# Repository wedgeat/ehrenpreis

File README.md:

# Ehrenpreis — electronic chime module

**A compact, programmable audio module for embedded projects, built around the NXP LPC802 microcontroller.**

Ehrenpreis explores a practical middle ground between a simple piezo buzzer and a full digital audio subsystem. It provides embedded projects with distinctive, programmable sound effects without a single board computer, an I²S audio interface or a dedicated high-performance audio processor.

The design uses a low-cost microcontroller to generate audio through PWM. A passive second-order RC low-pass filter reconstructs the signal, which is then AC-coupled and amplified by a dedicated audio amplifier. The firmware is written in C, with a lookup-table-based waveform generator and configurable sound envelopes.

The hardware and firmware are developed as an open project.

The repository is organised into two parts:

- hardware/ – Hardware design files for the electronic chime module.
- firmware/ – Embedded firmware for the LPC802 microcontroller.

A blog post on wedge.at documents the development process and the decisions behind the project.

License: BSD 3-Clause. See LICENSE for details.

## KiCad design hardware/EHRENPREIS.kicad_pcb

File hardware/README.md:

HARDWARE
Ehrenpreis Electronic Chime Module

This folder contains the hardware design files for the Ehrenpreis electronic chime module, built around the NXP LPC802 microcontroller.

The hardware is developed specifically for this project and forms the physical foundation of the electronic chime.

For an overview of the project and the development process, see the blog post on wedge.at.

See the repository root for general project information and licensing.

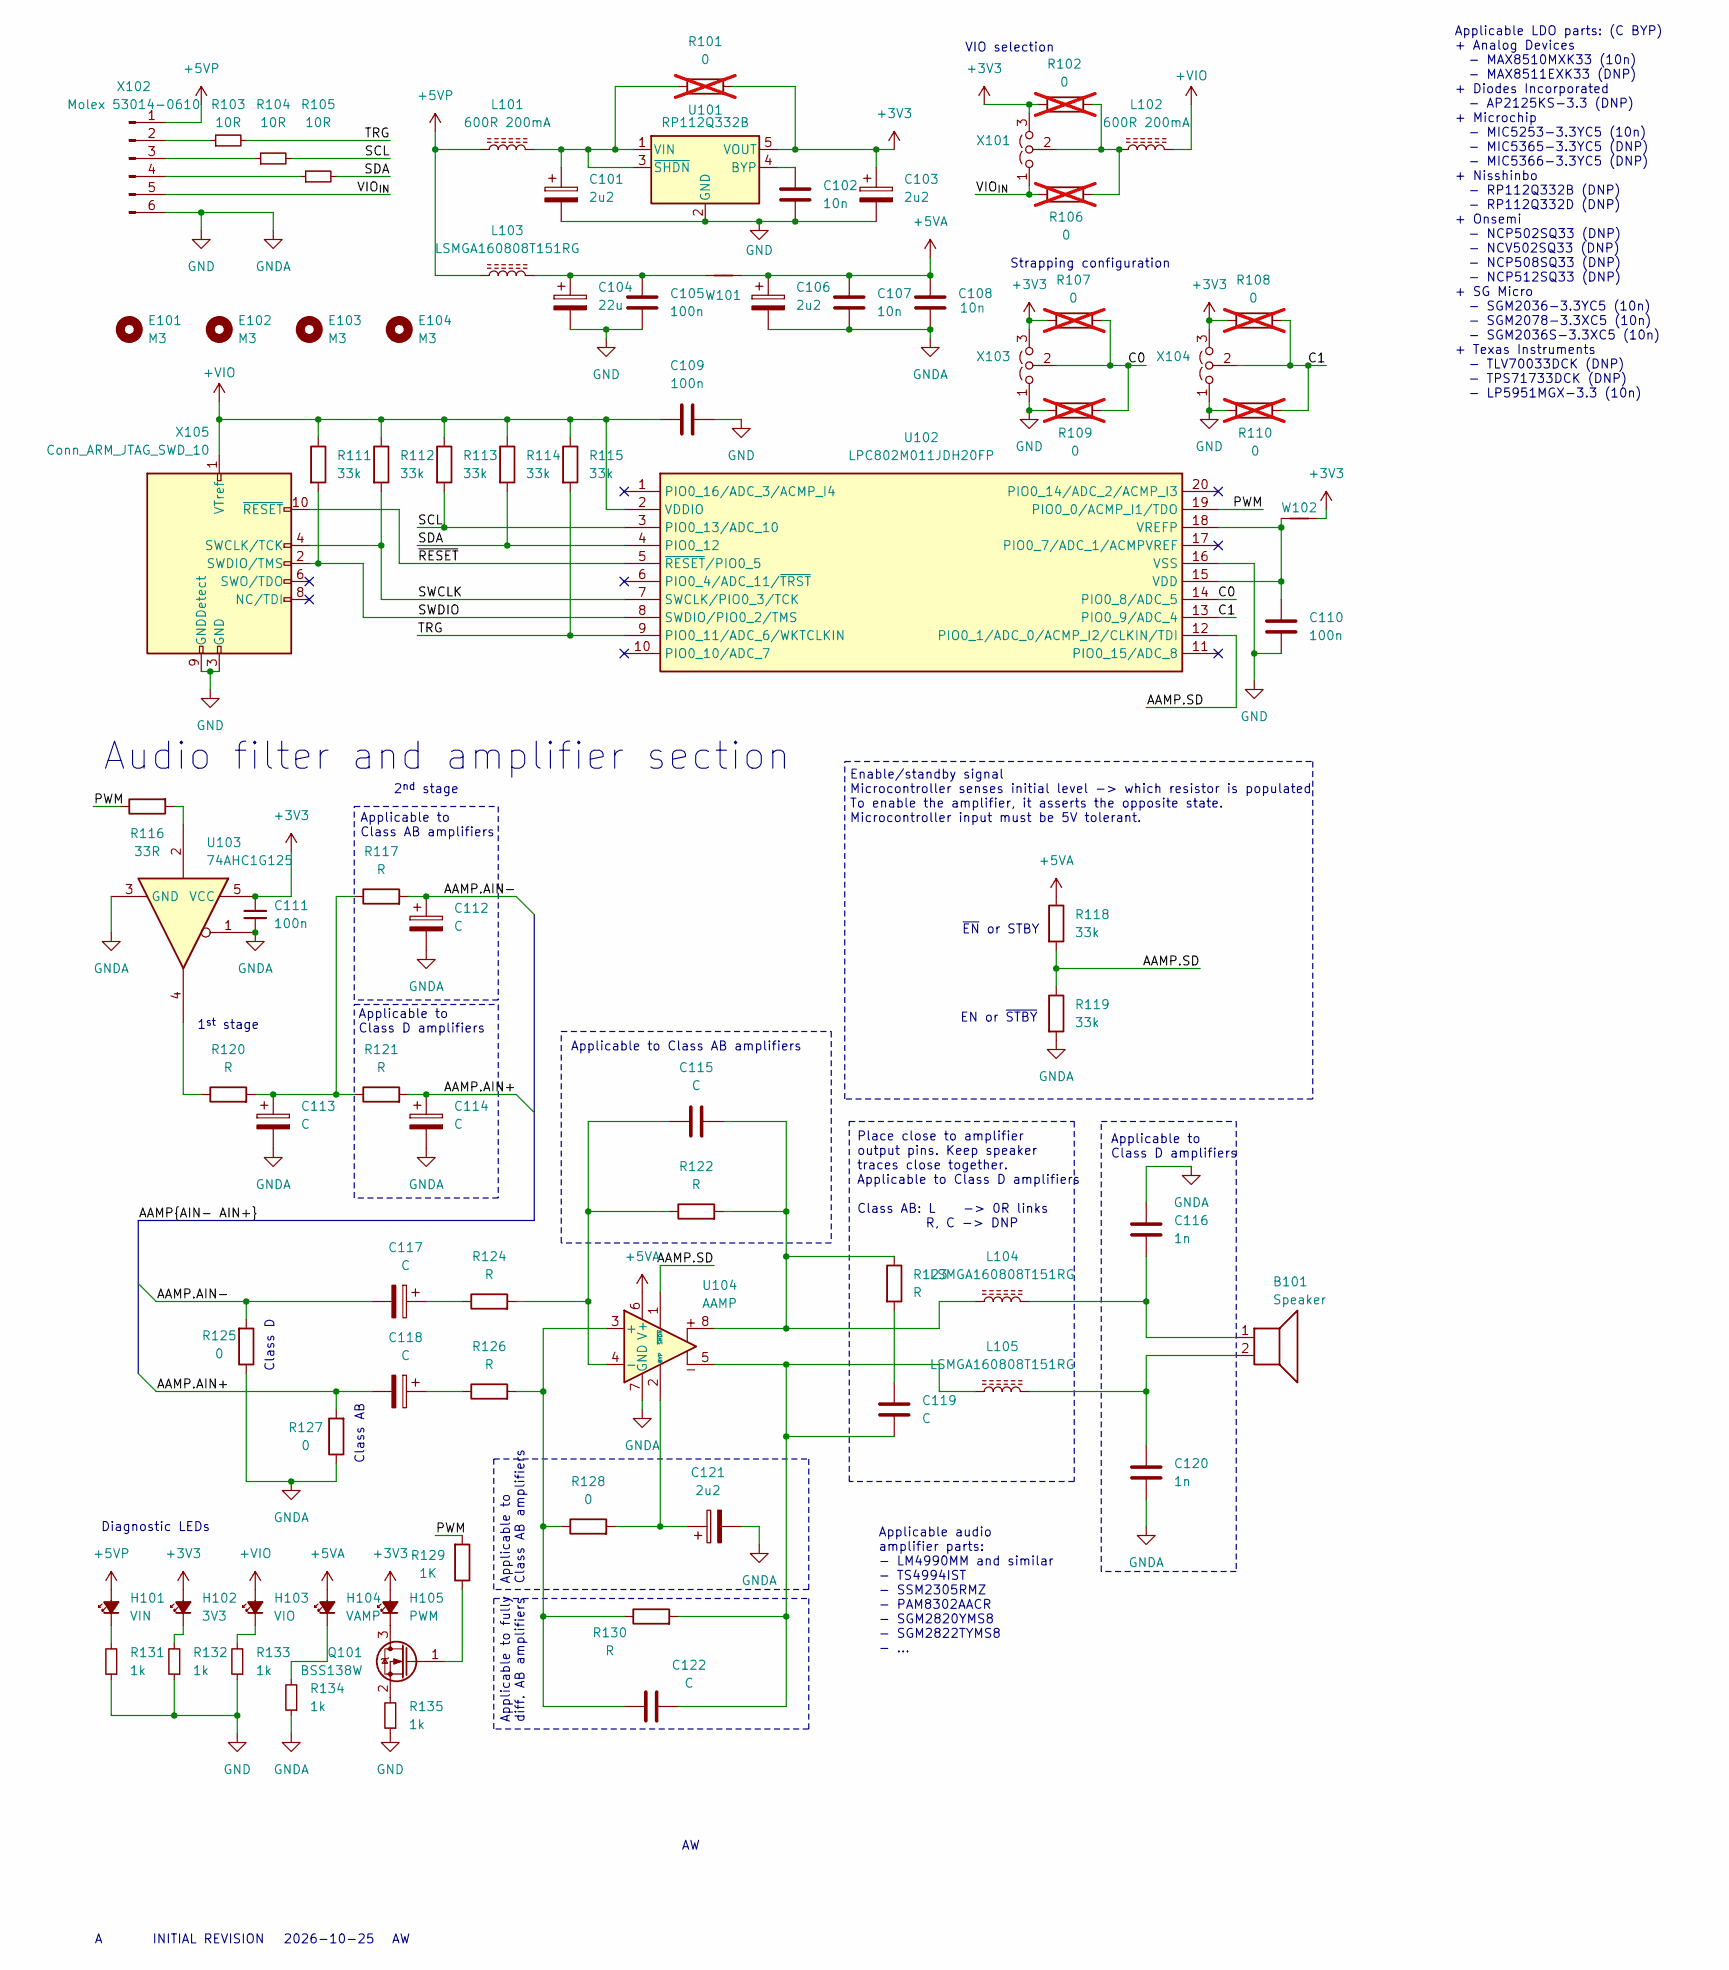
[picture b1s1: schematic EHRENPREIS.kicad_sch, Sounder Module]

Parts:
B101: Speaker; JST_XH_B2B-XH-A_1x02_P2.50mm_Vertical
C101, C103, C106, C121: 2u2; CP_EIA-3216-18_Kemet-A
C102, C107, C108: 10n; C_0603_1608Metric
C104: 22u; CP_EIA-7343-31_Kemet-D
C105, C109, C110, C111: 100n; C_0603_1608Metric
C112, C113, C114, C117, C118: C; CP_EIA-3216-18_Kemet-A
C115, C119, C122: C; C_0603_1608Metric
C116, C120: 1n; C_0603_1608Metric
E101, E102, E103, E104: M3; MountingHole_3.2mm_M3_DIN965
H101: VIN; LED_0603_1608Metric
H102: 3V3; LED_0603_1608Metric
H103: VIO; LED_0603_1608Metric
H104: VAMP; LED_0603_1608Metric
H105: PWM; LED_0603_1608Metric
L101, L102: 600R 200mA; L_0603_1608Metric
L103, L104, L105: LSMGA160808T151RG; L_0603_1608Metric
Q101: BSS138W; SOT-323_SC-70
R101, R102, R106, R107, R108, R109, R110: 0; R_0603_1608Metric; not fitted
R103, R104, R105: 10R; R_0603_1608Metric
R111, R112, R113, R114, R115, R118, R119: 33k; R_0603_1608Metric
R116: 33R; R_0603_1608Metric
R117, R120, R121, R122, R123, R124, R126, R130: R; R_0603_1608Metric
R125, R127, R128: 0; R_0603_1608Metric
R129: 1K; R_0603_1608Metric
R131, R132, R133, R134, R135: 1k; R_0603_1608Metric
U101: RP112Q332B; SOT-353_SC-70-5
U102: LPC802M011JDH20FP; TSSOP-20_4.4x6.5mm_P0.65mm; Manufacturer_Part_Number LPC802M011JDH20FP; Mouser Part Number 771-LPC802M011JDH20F
U103: 74AHC1G125; SOT-353_SC-70-5
U104: AAMP; TSSOP-8_3x3mm_P0.65mm
W101, W102: NetTie_2; NetTie-2_SMD_Pad0.5mm
X101: VIO; PinHeader_1x03_P2.54mm_Vertical
X102: Molex 53014-0610; SHDR6W60P0X200_1X6_1400X435X585P
X103: C0; PinHeader_1x03_P2.54mm_Vertical
X104: C1; PinHeader_1x03_P2.54mm_Vertical
X105: Conn_ARM_JTAG_SWD_10; PinHeader_2x05_P1.27mm_Vertical_SMD

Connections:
+3V3: C103.1, C111.1, H102.2 (A), H105.2 (A), R101.2, R102.2, R107.2, R108.2, U101.5 (VOUT), U103.5 (VCC), W102.1, X101.3 (B), X103.3 (B), X104.3 (B)
+5VA: C106.1, C107.1, C108.1, H104.2 (A), R118.1, U104.6 (V+), W101.1
+5VP: H101.2 (A), L101.1, L103.1, X102.1
+VIO: C109.1, H103.2 (A), L102.2, R111.1, R112.1, R113.1, R114.1, R115.1, U102.2 (VDDIO), X105.1 (VTref)
/AAMP.AIN+: C114.1, C118.2, R121.2, R127.2
/AAMP.AIN-: C112.1, C117.2, R117.2, R125.2
/AAMP.SD: R118.2, R119.1, U102.12 (PIO0_1/ADC_0/ACMP_I2/CLKIN/TDI), U104.1 (~SHDN)
/C0: R107.1, R109.1, U102.14 (PIO0_8/ADC_5), X103.2 (C)
/C1: R108.1, R110.1, U102.13 (PIO0_9/ADC_4), X104.2 (C)
/PWM: R116.1, R129.2, U102.19 (PIO0_0/ACMP_I1/TDO)
/SCL: R104.2, R113.2, U102.3 (PIO0_13/ADC_10)
/SDA: R105.2, R114.2, U102.4 (PIO0_12)
/SWCLK: R112.2, U102.7 (SWCLK/PIO0_3/TCK), X105.4 (SWCLK/TCK)
/SWDIO: R111.2, U102.8 (SWDIO/PIO0_2/TMS), X105.2 (SWDIO/TMS)
/TRG: R103.2, R115.2, U102.9 (PIO0_11/ADC_6/WKTCLKIN)
/VIO_{IN}: R106.2, X101.1 (A), X102.5
/~RESET: U102.5 (~RESET/PIO0_5), X105.10 (~RESET)
GND: C101.2, C102.2, C103.2, C104.2, C105.2, C106.2, C107.2, C108.2, C109.2, C110.2, C111.2, C112.2, C113.2, C114.2, C116.1, C120.2, C121.2, R109.2, R110.2, R119.2, R125.1, R127.1, R131.1, R132.1, R133.1, R134.1, R135.1, U101.2 (GND), U102.16 (VSS), U103.1, U103.3 (GND), U104.7 (GND), X102.6, X103.1 (A), X104.1 (A), X105.3 (GND), X105.5 (GND), X105.9 (GNDDetect)
unnamed: B101.1, C116.2, L104.2
unnamed: B101.2, C120.1, L105.2
unnamed: C104.1, C105.1, L103.2, W101.2
unnamed: C113.1, R117.1, R120.2, R121.1
unnamed: C115.2, L104.1, R122.2, R123.1, U104.8
unnamed: C117.1, R124.1
unnamed: C118.1, R126.1
unnamed: C119.1, R123.2
unnamed: C119.2, C122.2, L105.1, R130.2, U104.5
unnamed: H101.1 (K), R131.2
unnamed: H102.1 (K), R132.2
unnamed: H103.1 (K), R133.2
unnamed: H104.1 (K), R134.2
unnamed: H105.1 (K), Q101.3 (D)
unnamed: Q101.1 (G), R129.1
unnamed: Q101.2 (S), R135.2
unnamed: R116.2, U103.2
unnamed: R120.1, U103.4
unnamed: C102.1, U101.4 (BYP)
unnamed: C101.1, L101.2, R101.1, U101.1 (VIN), U101.3 (~SHDN)
unnamed: C110.1, U102.15 (VDD), U102.18 (VREFP), W102.2
unnamed: C122.1, R126.2, R128.1, R130.1, U104.3 (+)
unnamed: C115.1, R122.1, R124.2, U104.4 (-)
unnamed: C121.1, R128.2, U104.2 (BYP)
unnamed: L102.1, R102.1, R106.1, X101.2 (C)
unnamed: R103.1, X102.2
unnamed: R104.1, X102.3
unnamed: R105.1, X102.4

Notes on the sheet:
2^{nd} stage
Applicable to Class D amplifiers
Place close to amplifier output pins. Keep speaker traces close together. Applicable to Class D amplifiers Class AB: L -> 0R links R, C -> DNP
Diagnostic LEDs
1^{st} stage
EN or ~{STBY}
Applicable to fully diff. AB amplifiers
Class D
Class AB
Strapping configuration
Audio filter and amplifier section
2026-10-25
Applicable to Class AB amplifiers
Applicable to Class AB amplifiers
Applicable LDO parts: (C BYP) + Analog Devices - MAX8510MXK33 (10n) - MAX8511EXK33 (DNP) + Diodes Incorporated - AP2125KS-3.3 (DNP) + Microchip - MIC5253-3.3YC5 (10n) - MIC5365-3.3YC5 (DNP) - MIC5366-3.3YC5 (DNP) + Nisshinbo - RP112Q332B (DNP) - RP112Q332D (DNP) + Onsemi - NCP502SQ33 (DNP) - NCV502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
~{EN} or STBY
VIO selection
INITIAL REVISION
Enable/standby signal Microcontroller senses initial level -> which resistor is populated To enable the amplifier, it asserts the opposite state. Microcontroller input must be 5V tolerant.
Applicable audio amplifier parts: - LM4990MM and similar - TS4994IST - SSM2305RMZ - PAM8302AACR - SGM2820YMS8 - SGM2822TYMS8 - ...

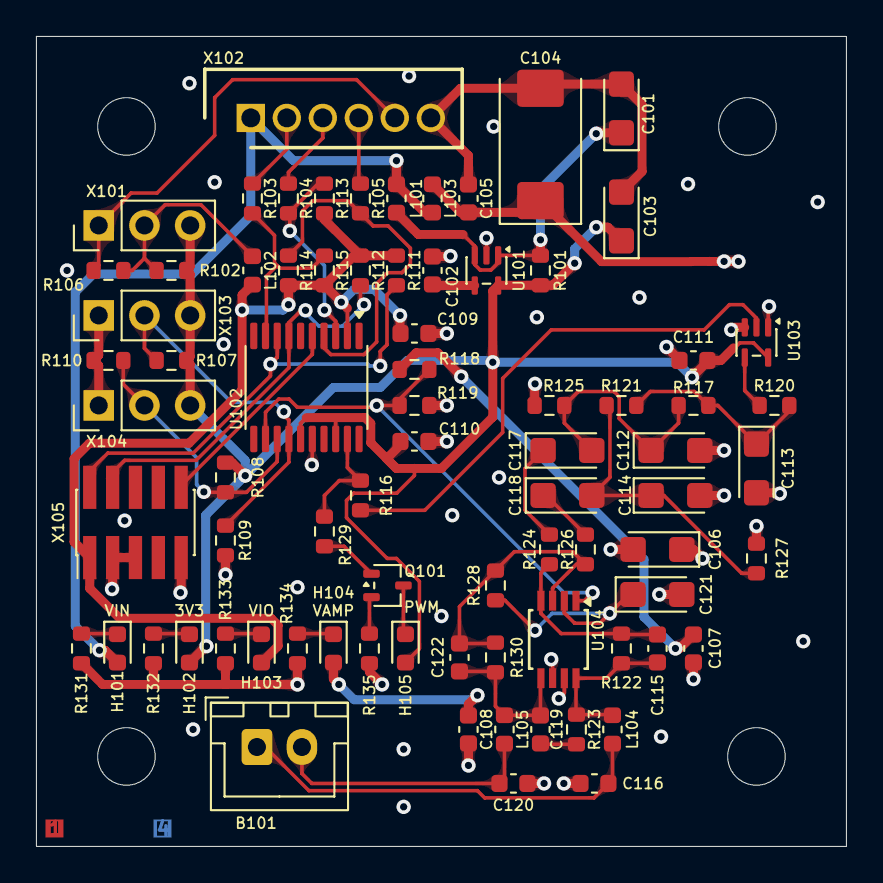
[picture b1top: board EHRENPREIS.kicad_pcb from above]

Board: 4 copper layers, 45.0 x 45.0 mm, 84 parts (0 on the bottom side), 46 nets.
